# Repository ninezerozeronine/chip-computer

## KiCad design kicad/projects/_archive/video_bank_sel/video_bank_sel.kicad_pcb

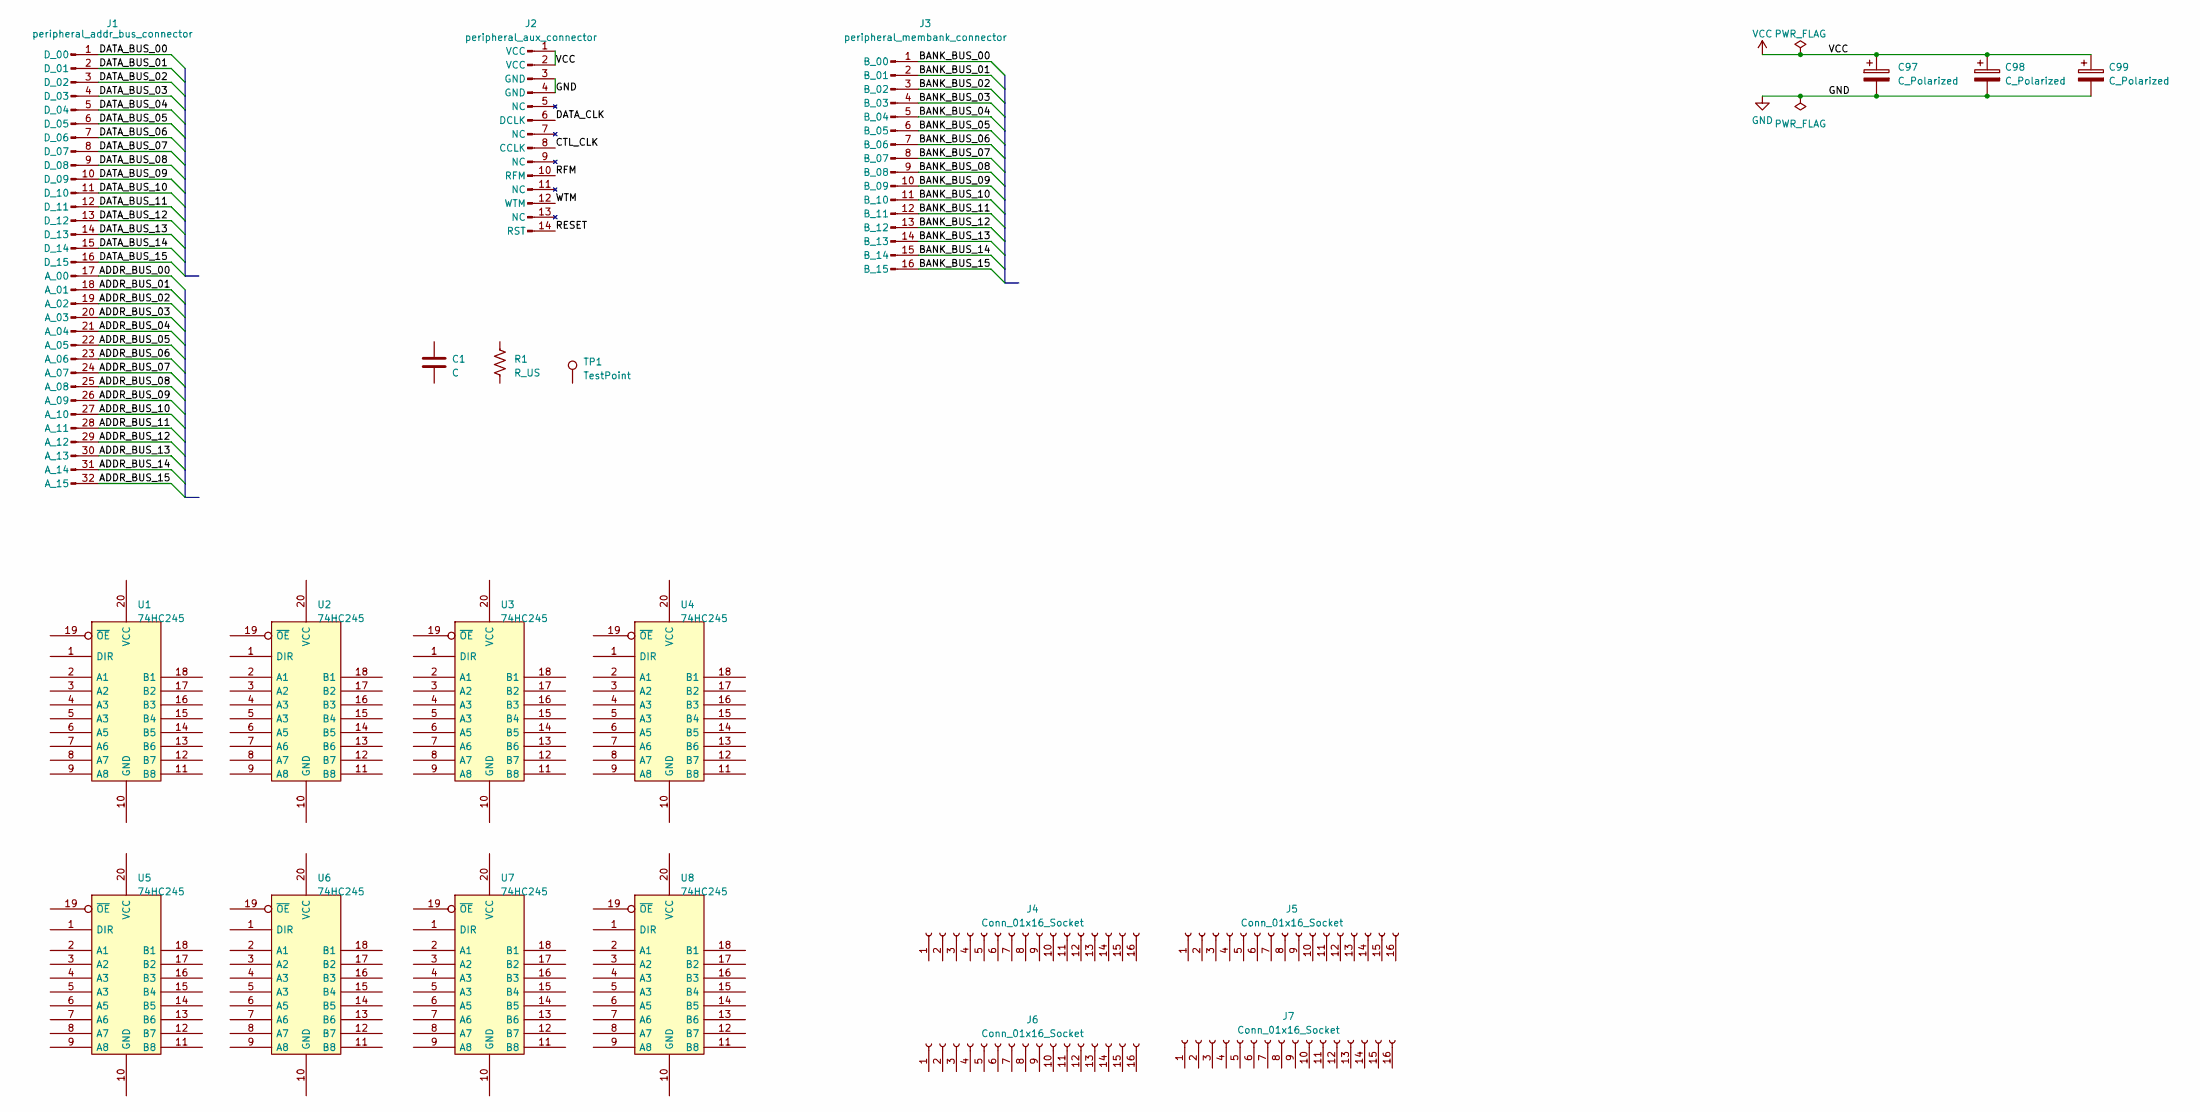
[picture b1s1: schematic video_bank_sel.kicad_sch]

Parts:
C1: C; C_Disc_D5.0mm_W2.5mm_P5.00mm
C97, C98, C99: C_Polarized; CP_Radial_D6.3mm_P2.50mm
J1: peripheral_addr_bus_connector; peripheral-backplane-data-addr-anno
J2: peripheral_aux_connector; peripheral-backplane-aux
J3: peripheral_membank_connector; peripheral-backplane-membank
J4, J5, J6, J7: Conn_01x16_Socket; PinSocket_1x16_P2.54mm_Horizontal
R1: R_US; R_Axial_DIN0207_L6.3mm_D2.5mm_P10.16mm_Horizontal
TP1: TestPoint; Pin_D1.0mm_L10.0mm
U1, U2, U3, U4, U5, U6, U7, U8: 74HC245; DIP-20_W7.62mm_Socket

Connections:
/ADDR_BUS_00: J1.17 (A_00)
/ADDR_BUS_01: J1.18 (A_01)
/ADDR_BUS_02: J1.19 (A_02)
/ADDR_BUS_03: J1.20 (A_03)
/ADDR_BUS_04: J1.21 (A_04)
/ADDR_BUS_05: J1.22 (A_05)
/ADDR_BUS_06: J1.23 (A_06)
/ADDR_BUS_07: J1.24 (A_07)
/ADDR_BUS_08: J1.25 (A_08)
/ADDR_BUS_09: J1.26 (A_09)
/ADDR_BUS_10: J1.27 (A_10)
/ADDR_BUS_11: J1.28 (A_11)
/ADDR_BUS_12: J1.29 (A_12)
/ADDR_BUS_13: J1.30 (A_13)
/ADDR_BUS_14: J1.31 (A_14)
/ADDR_BUS_15: J1.32 (A_15)
/BANK_BUS_00: J3.1 (B_00)
/BANK_BUS_01: J3.2 (B_01)
/BANK_BUS_02: J3.3 (B_02)
/BANK_BUS_03: J3.4 (B_03)
/BANK_BUS_04: J3.5 (B_04)
/BANK_BUS_05: J3.6 (B_05)
/BANK_BUS_06: J3.7 (B_06)
/BANK_BUS_07: J3.8 (B_07)
/BANK_BUS_08: J3.9 (B_08)
/BANK_BUS_09: J3.10 (B_09)
/BANK_BUS_10: J3.11 (B_10)
/BANK_BUS_11: J3.12 (B_11)
/BANK_BUS_12: J3.13 (B_12)
/BANK_BUS_13: J3.14 (B_13)
/BANK_BUS_14: J3.15 (B_14)
/BANK_BUS_15: J3.16 (B_15)
/CTL_CLK: J2.8 (CCLK)
/DATA_BUS_00: J1.1 (D_00)
/DATA_BUS_01: J1.2 (D_01)
/DATA_BUS_02: J1.3 (D_02)
/DATA_BUS_03: J1.4 (D_03)
/DATA_BUS_04: J1.5 (D_04)
/DATA_BUS_05: J1.6 (D_05)
/DATA_BUS_06: J1.7 (D_06)
/DATA_BUS_07: J1.8 (D_07)
/DATA_BUS_08: J1.9 (D_08)
/DATA_BUS_09: J1.10 (D_09)
/DATA_BUS_10: J1.11 (D_10)
/DATA_BUS_11: J1.12 (D_11)
/DATA_BUS_12: J1.13 (D_12)
/DATA_BUS_13: J1.14 (D_13)
/DATA_BUS_14: J1.15 (D_14)
/DATA_BUS_15: J1.16 (D_15)
/DATA_CLK: J2.6 (DCLK)
/RESET: J2.14 (RST)
/RFM: J2.10 (RFM)
/WTM: J2.12 (WTM)
GND: C97.2, C98.2, C99.2, J2.3 (GND), J2.4 (GND)
VCC: C97.1, C98.1, C99.1, J2.1 (VCC), J2.2 (VCC)

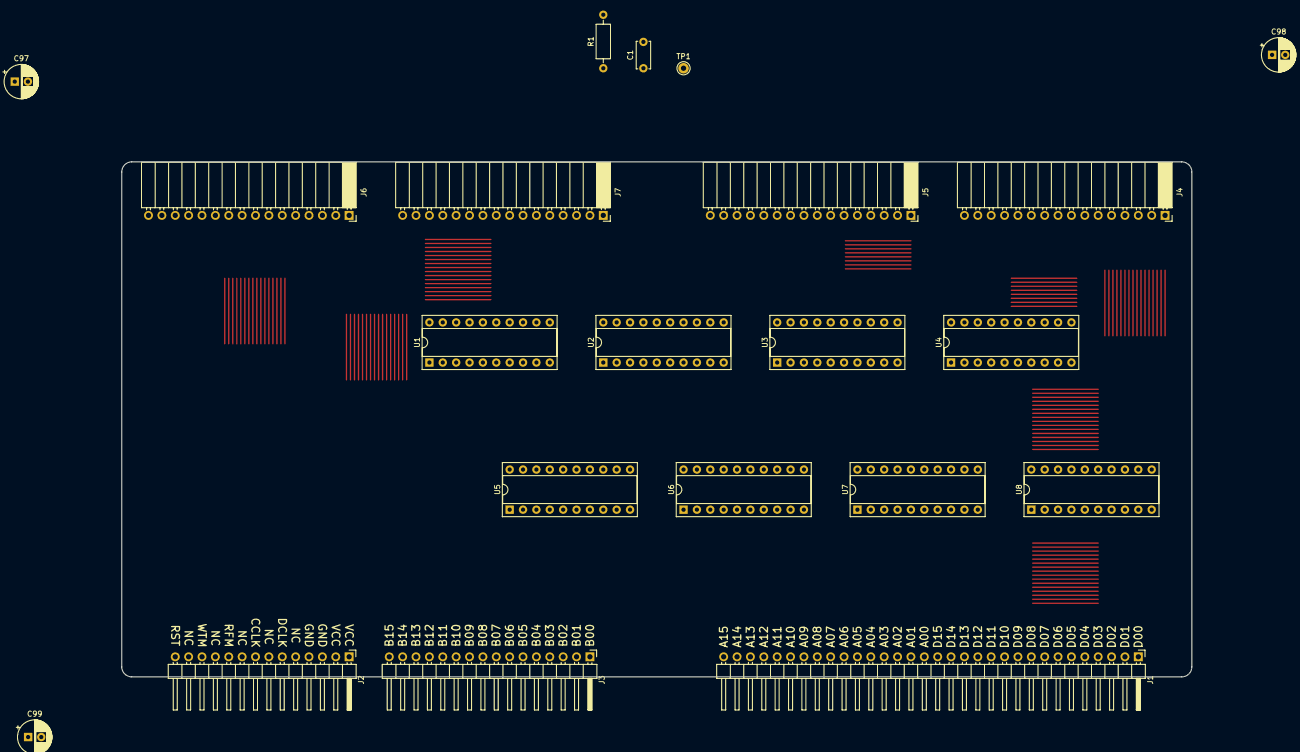
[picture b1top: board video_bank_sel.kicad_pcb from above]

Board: 2 copper layers, 203.2 x 97.8 mm, 21 parts (0 on the bottom side), 2 nets.

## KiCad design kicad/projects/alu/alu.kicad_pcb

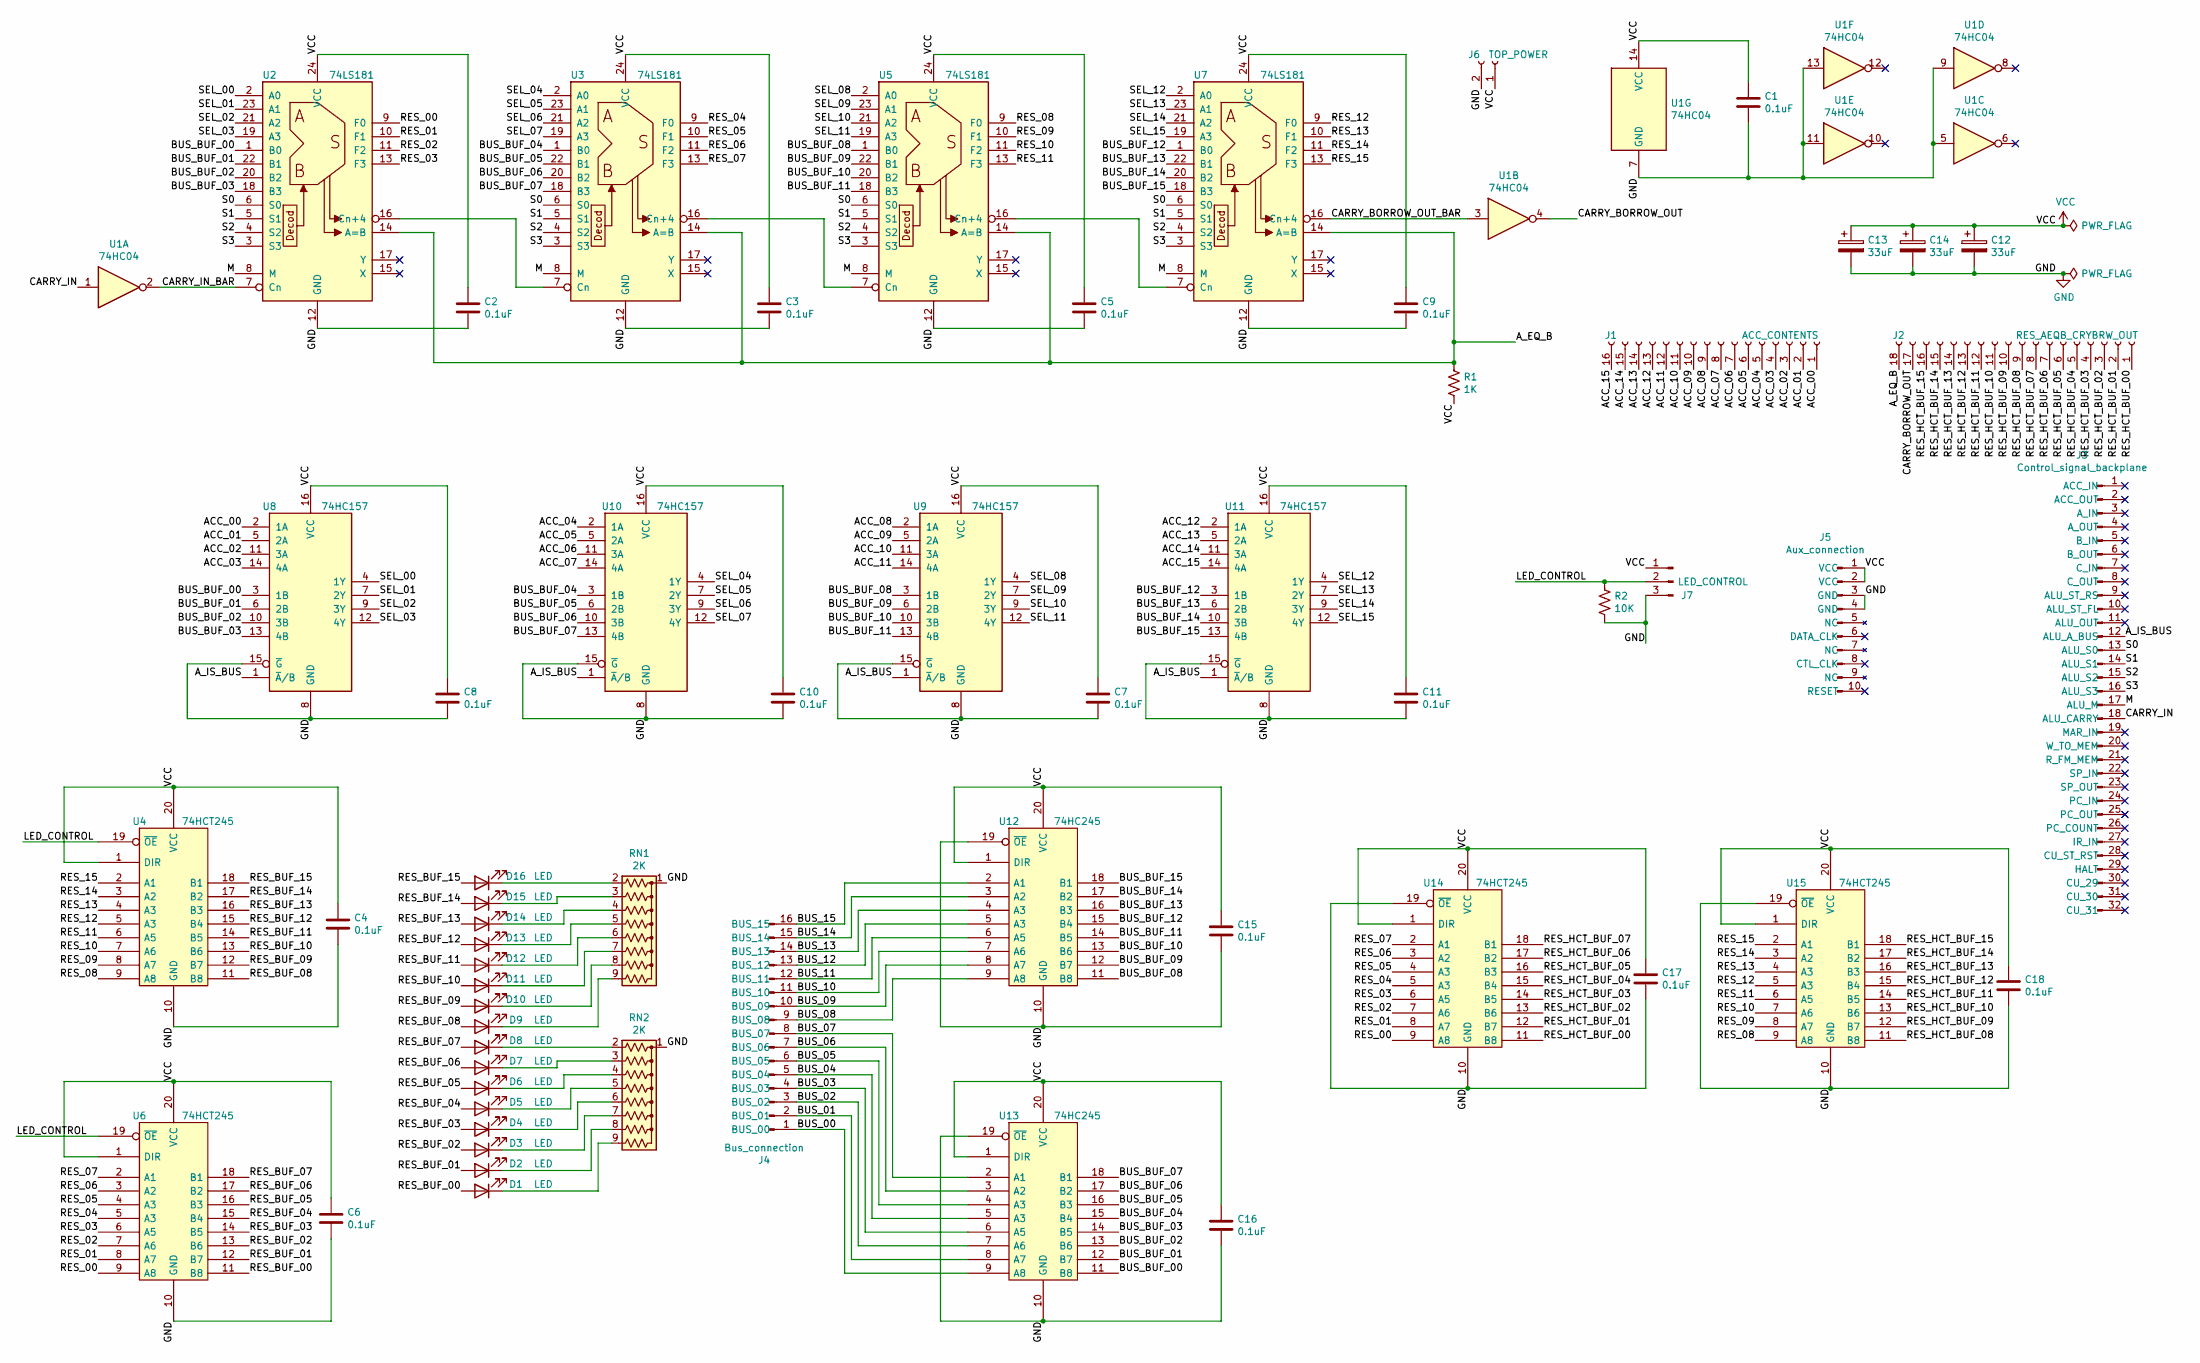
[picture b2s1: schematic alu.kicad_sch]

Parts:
C1, C2, C3, C4, C5, C6, C7, C8, C9, C10, C11, C15, C16, C17, C18: 0.1uF; C_Disc_D4.7mm_W2.5mm_P5.00mm
C12, C13, C14: 33uF; CP_Radial_D6.3mm_P2.50mm
D1, D2, D3, D4, D5, D6, D7, D8, D9, D10, D11, D12, D13, D14, D15, D16: LED; LED_D5.0mm_Horizontal_O3.81mm_Z3.0mm
J1: ACC_CONTENTS; PinSocket_1x16_P2.54mm_Horizontal
J2: RES_AEQB_CRYBRW_OUT; PinSocket_1x18_P2.54mm_Horizontal
J3: Control_signal_backplane; backplane-connector-single-row-annotated
J4: Bus_connection; bus-connection
J5: Aux_connection; aux-connection
J6: TOP_POWER; PinSocket_1x02_P2.54mm_Horizontal
J7: LED_CONTROL; PinHeader_1x03_P2.54mm_Horizontal
R1: 1K; R_Axial_DIN0207_L6.3mm_D2.5mm_P10.16mm_Horizontal
R2: 10K; R_Axial_DIN0207_L6.3mm_D2.5mm_P10.16mm_Horizontal
RN1, RN2: 2K; R_Array_SIP9
U1: 74HC04; DIP-14_W7.62mm_Socket
U2, U3, U5, U7: 74LS181; DIP-24_W15.24mm_Socket
U4, U6, U14, U15: 74HCT245; DIP-20_W7.62mm_Socket
U8, U9, U10, U11: 74HC157; DIP-16_W7.62mm_Socket
U12, U13: 74HC245; DIP-20_W7.62mm_Socket

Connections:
/ACC_00: J1.1, U8.2 (1A)
/ACC_01: J1.2, U8.5 (2A)
/ACC_02: J1.3, U8.11 (3A)
/ACC_03: J1.4, U8.14 (4A)
/ACC_04: J1.5, U10.2 (1A)
/ACC_05: J1.6, U10.5 (2A)
/ACC_06: J1.7, U10.11 (3A)
/ACC_07: J1.8, U10.14 (4A)
/ACC_08: J1.9, U9.2 (1A)
/ACC_09: J1.10, U9.5 (2A)
/ACC_10: J1.11, U9.11 (3A)
/ACC_11: J1.12, U9.14 (4A)
/ACC_12: J1.13, U11.2 (1A)
/ACC_13: J1.14, U11.5 (2A)
/ACC_14: J1.15, U11.11 (3A)
/ACC_15: J1.16, U11.14 (4A)
/A_EQ_B: J2.18, R1.1, U2.14 (A=B), U3.14 (A=B), U5.14 (A=B), U7.14 (A=B)
/A_IS_BUS: J3.12 (ALU_A_BUS), U8.1 (~A/B), U9.1 (~A/B), U10.1 (~A/B), U11.1 (~A/B)
/BUS_00: J4.1 (BUS_00), U13.9 (A8)
/BUS_01: J4.2 (BUS_01), U13.8 (A7)
/BUS_02: J4.3 (BUS_02), U13.7 (A6)
/BUS_03: J4.4 (BUS_03), U13.6 (A5)
/BUS_04: J4.5 (BUS_04), U13.5 (A3)
/BUS_05: J4.6 (BUS_05), U13.4 (A3)
/BUS_06: J4.7 (BUS_06), U13.3 (A2)
/BUS_07: J4.8 (BUS_07), U13.2 (A1)
/BUS_08: J4.9 (BUS_08), U12.9 (A8)
/BUS_09: J4.10 (BUS_09), U12.8 (A7)
/BUS_10: J4.11 (BUS_10), U12.7 (A6)
/BUS_11: J4.12 (BUS_11), U12.6 (A5)
/BUS_12: J4.13 (BUS_12), U12.5 (A3)
/BUS_13: J4.14 (BUS_13), U12.4 (A3)
/BUS_14: J4.15 (BUS_14), U12.3 (A2)
/BUS_15: J4.16 (BUS_15), U12.2 (A1)
/BUS_BUF_00: U2.1 (B0), U8.3 (1B), U13.11 (B8)
/BUS_BUF_01: U2.22 (B1), U8.6 (2B), U13.12 (B7)
/BUS_BUF_02: U2.20 (B2), U8.10 (3B), U13.13 (B6)
/BUS_BUF_03: U2.18 (B3), U8.13 (4B), U13.14 (B5)
/BUS_BUF_04: U3.1 (B0), U10.3 (1B), U13.15 (B4)
/BUS_BUF_05: U3.22 (B1), U10.6 (2B), U13.16 (B3)
/BUS_BUF_06: U3.20 (B2), U10.10 (3B), U13.17 (B2)
/BUS_BUF_07: U3.18 (B3), U10.13 (4B), U13.18 (B1)
/BUS_BUF_08: U5.1 (B0), U9.3 (1B), U12.11 (B8)
/BUS_BUF_09: U5.22 (B1), U9.6 (2B), U12.12 (B7)
/BUS_BUF_10: U5.20 (B2), U9.10 (3B), U12.13 (B6)
/BUS_BUF_11: U5.18 (B3), U9.13 (4B), U12.14 (B5)
/BUS_BUF_12: U7.1 (B0), U11.3 (1B), U12.15 (B4)
/BUS_BUF_13: U7.22 (B1), U11.6 (2B), U12.16 (B3)
/BUS_BUF_14: U7.20 (B2), U11.10 (3B), U12.17 (B2)
/BUS_BUF_15: U7.18 (B3), U11.13 (4B), U12.18 (B1)
/CARRY_BORROW_OUT: J2.17, U1.4
/CARRY_BORROW_OUT_BAR: U1.3, U7.16 (Cn+4)
/CARRY_IN: J3.18 (ALU_CARRY), U1.1
/CARRY_IN_BAR: U1.2, U2.7 (Cn)
/LED_CONTROL: J7.2, R2.1, U4.19 (~OE), U6.19 (~OE)
/M: J3.17 (ALU_M), U2.8 (M), U3.8 (M), U5.8 (M), U7.8 (M)
/RES_00: U2.9 (F0), U6.9 (A8), U14.9 (A8)
/RES_01: U2.10 (F1), U6.8 (A7), U14.8 (A7)
/RES_02: U2.11 (F2), U6.7 (A6), U14.7 (A6)
/RES_03: U2.13 (F3), U6.6 (A5), U14.6 (A5)
/RES_04: U3.9 (F0), U6.5 (A3), U14.5 (A3)
/RES_05: U3.10 (F1), U6.4 (A3), U14.4 (A3)
/RES_06: U3.11 (F2), U6.3 (A2), U14.3 (A2)
/RES_07: U3.13 (F3), U6.2 (A1), U14.2 (A1)
/RES_08: U4.9 (A8), U5.9 (F0), U15.9 (A8)
/RES_09: U4.8 (A7), U5.10 (F1), U15.8 (A7)
/RES_10: U4.7 (A6), U5.11 (F2), U15.7 (A6)
/RES_11: U4.6 (A5), U5.13 (F3), U15.6 (A5)
/RES_12: U4.5 (A3), U7.9 (F0), U15.5 (A3)
/RES_13: U4.4 (A3), U7.10 (F1), U15.4 (A3)
/RES_14: U4.3 (A2), U7.11 (F2), U15.3 (A2)
/RES_15: U4.2 (A1), U7.13 (F3), U15.2 (A1)
/RES_BUF_00: D1.2 (A), U6.11 (B8)
/RES_BUF_01: D2.2 (A), U6.12 (B7)
/RES_BUF_02: D3.2 (A), U6.13 (B6)
/RES_BUF_03: D4.2 (A), U6.14 (B5)
/RES_BUF_04: D5.2 (A), U6.15 (B4)
/RES_BUF_05: D6.2 (A), U6.16 (B3)
/RES_BUF_06: D7.2 (A), U6.17 (B2)
/RES_BUF_07: D8.2 (A), U6.18 (B1)
/RES_BUF_08: D9.2 (A), U4.11 (B8)
/RES_BUF_09: D10.2 (A), U4.12 (B7)
/RES_BUF_10: D11.2 (A), U4.13 (B6)
/RES_BUF_11: D12.2 (A), U4.14 (B5)
/RES_BUF_12: D13.2 (A), U4.15 (B4)
/RES_BUF_13: D14.2 (A), U4.16 (B3)
/RES_BUF_14: D15.2 (A), U4.17 (B2)
/RES_BUF_15: D16.2 (A), U4.18 (B1)
/RES_HCT_BUF_00: J2.1, U14.11 (B8)
/RES_HCT_BUF_01: J2.2, U14.12 (B7)
/RES_HCT_BUF_02: J2.3, U14.13 (B6)
/RES_HCT_BUF_03: J2.4, U14.14 (B5)
/RES_HCT_BUF_04: J2.5, U14.15 (B4)
/RES_HCT_BUF_05: J2.6, U14.16 (B3)
/RES_HCT_BUF_06: J2.7, U14.17 (B2)
/RES_HCT_BUF_07: J2.8, U14.18 (B1)
/RES_HCT_BUF_08: J2.9, U15.11 (B8)
/RES_HCT_BUF_09: J2.10, U15.12 (B7)
/RES_HCT_BUF_10: J2.11, U15.13 (B6)
/RES_HCT_BUF_11: J2.12, U15.14 (B5)
/RES_HCT_BUF_12: J2.13, U15.15 (B4)
/RES_HCT_BUF_13: J2.14, U15.16 (B3)
/RES_HCT_BUF_14: J2.15, U15.17 (B2)
/RES_HCT_BUF_15: J2.16, U15.18 (B1)
/S0: J3.13 (ALU_S0), U2.6 (S0), U3.6 (S0), U5.6 (S0), U7.6 (S0)
/S1: J3.14 (ALU_S1), U2.5 (S1), U3.5 (S1), U5.5 (S1), U7.5 (S1)
/S2: J3.15 (ALU_S2), U2.4 (S2), U3.4 (S2), U5.4 (S2), U7.4 (S2)
/S3: J3.16 (ALU_S3), U2.3 (S3), U3.3 (S3), U5.3 (S3), U7.3 (S3)
/SEL_00: U2.2 (A0), U8.4 (1Y)
/SEL_01: U2.23 (A1), U8.7 (2Y)
/SEL_02: U2.21 (A2), U8.9 (3Y)
/SEL_03: U2.19 (A3), U8.12 (4Y)
/SEL_04: U3.2 (A0), U10.4 (1Y)
/SEL_05: U3.23 (A1), U10.7 (2Y)
/SEL_06: U3.21 (A2), U10.9 (3Y)
/SEL_07: U3.19 (A3), U10.12 (4Y)
/SEL_08: U5.2 (A0), U9.4 (1Y)
/SEL_09: U5.23 (A1), U9.7 (2Y)
/SEL_10: U5.21 (A2), U9.9 (3Y)
/SEL_11: U5.19 (A3), U9.12 (4Y)
/SEL_12: U7.2 (A0), U11.4 (1Y)
/SEL_13: U7.23 (A1), U11.7 (2Y)
/SEL_14: U7.21 (A2), U11.9 (3Y)
/SEL_15: U7.19 (A3), U11.12 (4Y)
GND: C1.2, C2.2, C3.2, C4.2, C5.2, C6.2, C7.2, C8.2, C9.2, C10.2, C11.2, C12.2, C13.2, C14.2, C15.2, C16.2, C17.2, C18.2, J5.3 (GND), J5.4 (GND), J6.2, J7.3, R2.2, RN1.1 (common), RN2.1 (common), U1.5, U1.7 (GND), U1.9, U1.11, U1.13, U2.12 (GND), U3.12 (GND), U4.10 (GND), U5.12 (GND), U6.10 (GND), U7.12 (GND), U8.8 (GND), U8.15 (~G), U9.8 (GND), U9.15 (~G), U10.8 (GND), U10.15 (~G), U11.8 (GND), U11.15 (~G), U12.10 (GND), U12.19 (~OE), U13.10 (GND), U13.19 (~OE), U14.10 (GND), U14.19 (~OE), U15.10 (GND), U15.19 (~OE)
unnamed: D1.1 (K), RN2.9 (R8)
unnamed: D2.1 (K), RN2.8 (R7)
unnamed: D3.1 (K), RN2.7 (R6)
unnamed: D4.1 (K), RN2.6 (R5)
unnamed: D5.1 (K), RN2.5 (R4)
unnamed: D6.1 (K), RN2.4 (R3)
unnamed: D7.1 (K), RN2.3 (R2)
unnamed: D8.1 (K), RN2.2 (R1)
unnamed: D9.1 (K), RN1.9 (R8)
unnamed: D10.1 (K), RN1.8 (R7)
unnamed: D11.1 (K), RN1.7 (R6)
unnamed: D12.1 (K), RN1.6 (R5)
unnamed: D13.1 (K), RN1.5 (R4)
unnamed: D14.1 (K), RN1.4 (R3)
unnamed: D15.1 (K), RN1.3 (R2)
unnamed: D16.1 (K), RN1.2 (R1)
unnamed: U2.16 (Cn+4), U3.7 (Cn)
unnamed: U3.16 (Cn+4), U5.7 (Cn)
unnamed: U5.16 (Cn+4), U7.7 (Cn)
VCC: C1.1, C2.1, C3.1, C4.1, C5.1, C6.1, C7.1, C8.1, C9.1, C10.1, C11.1, C12.1, C13.1, C14.1, C15.1, C16.1, C17.1, C18.1, J5.1 (VCC), J5.2 (VCC), J6.1, J7.1, R1.2, U1.14 (VCC), U2.24 (VCC), U3.24 (VCC), U4.1 (DIR), U4.20 (VCC), U5.24 (VCC), U6.1 (DIR), U6.20 (VCC), U7.24 (VCC), U8.16 (VCC), U9.16 (VCC), U10.16 (VCC), U11.16 (VCC), U12.1 (DIR), U12.20 (VCC), U13.1 (DIR), U13.20 (VCC), U14.1 (DIR), U14.20 (VCC), U15.1 (DIR), U15.20 (VCC)

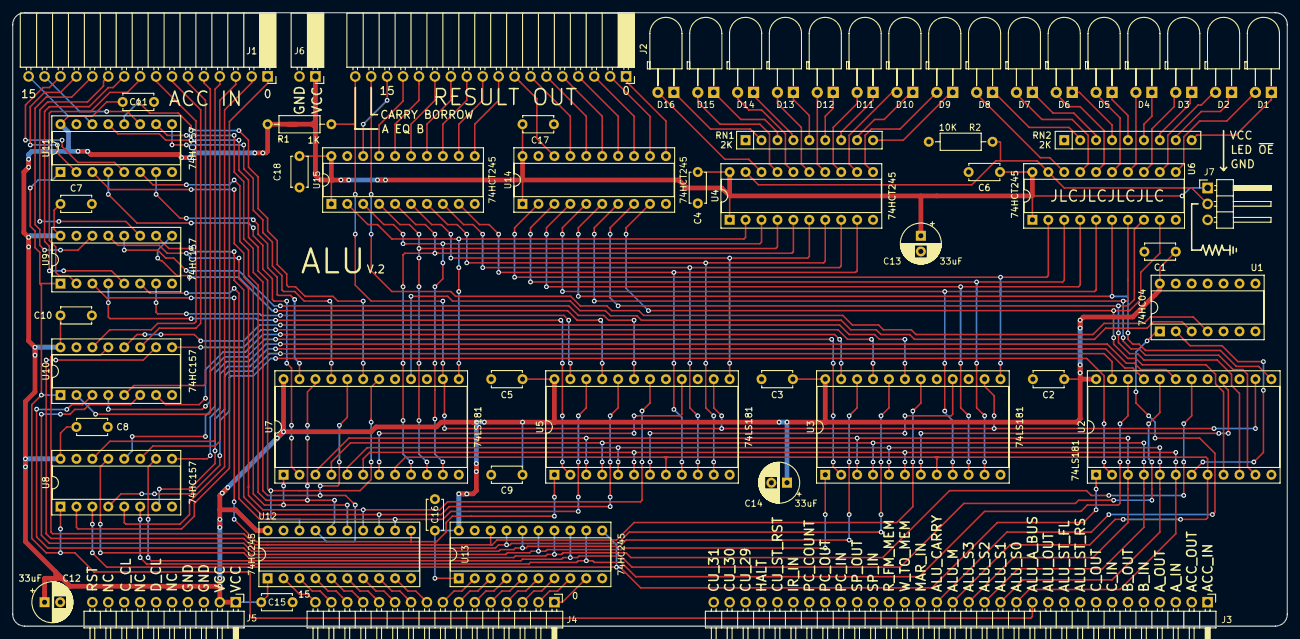
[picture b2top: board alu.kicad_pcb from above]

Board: 2 copper layers, 203.2 x 97.8 mm, 60 parts (0 on the bottom side), 145 nets.

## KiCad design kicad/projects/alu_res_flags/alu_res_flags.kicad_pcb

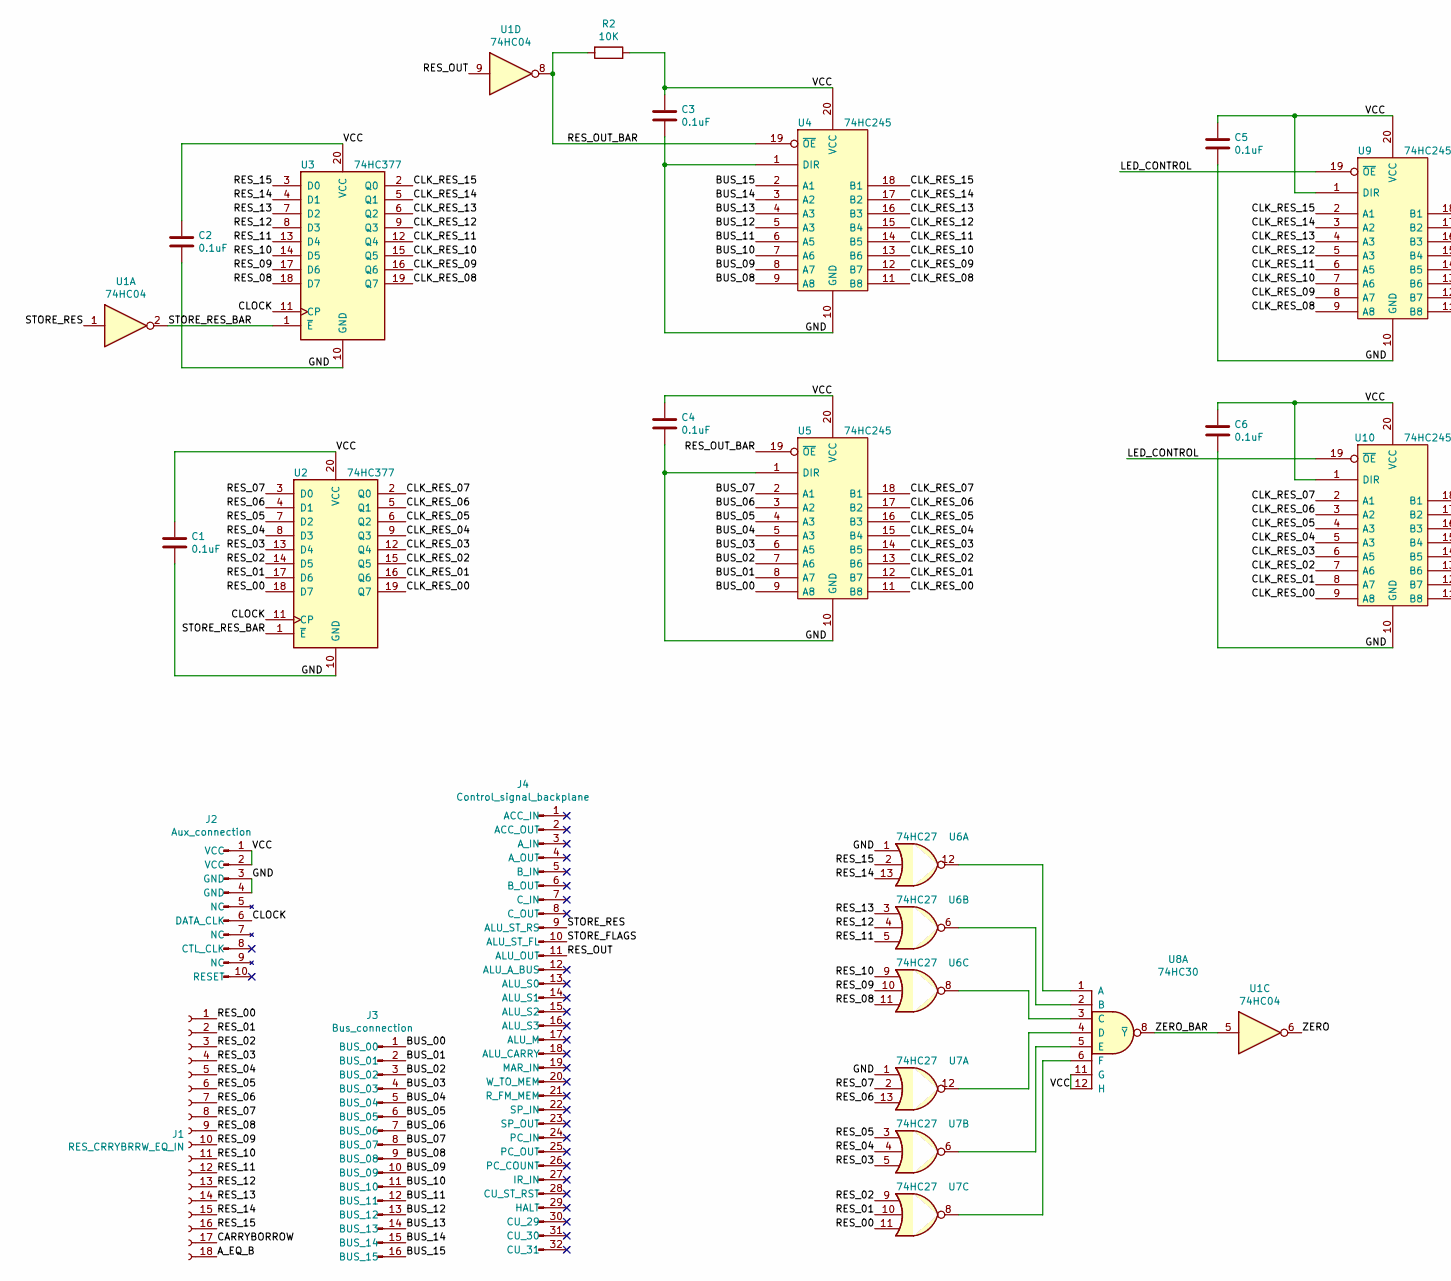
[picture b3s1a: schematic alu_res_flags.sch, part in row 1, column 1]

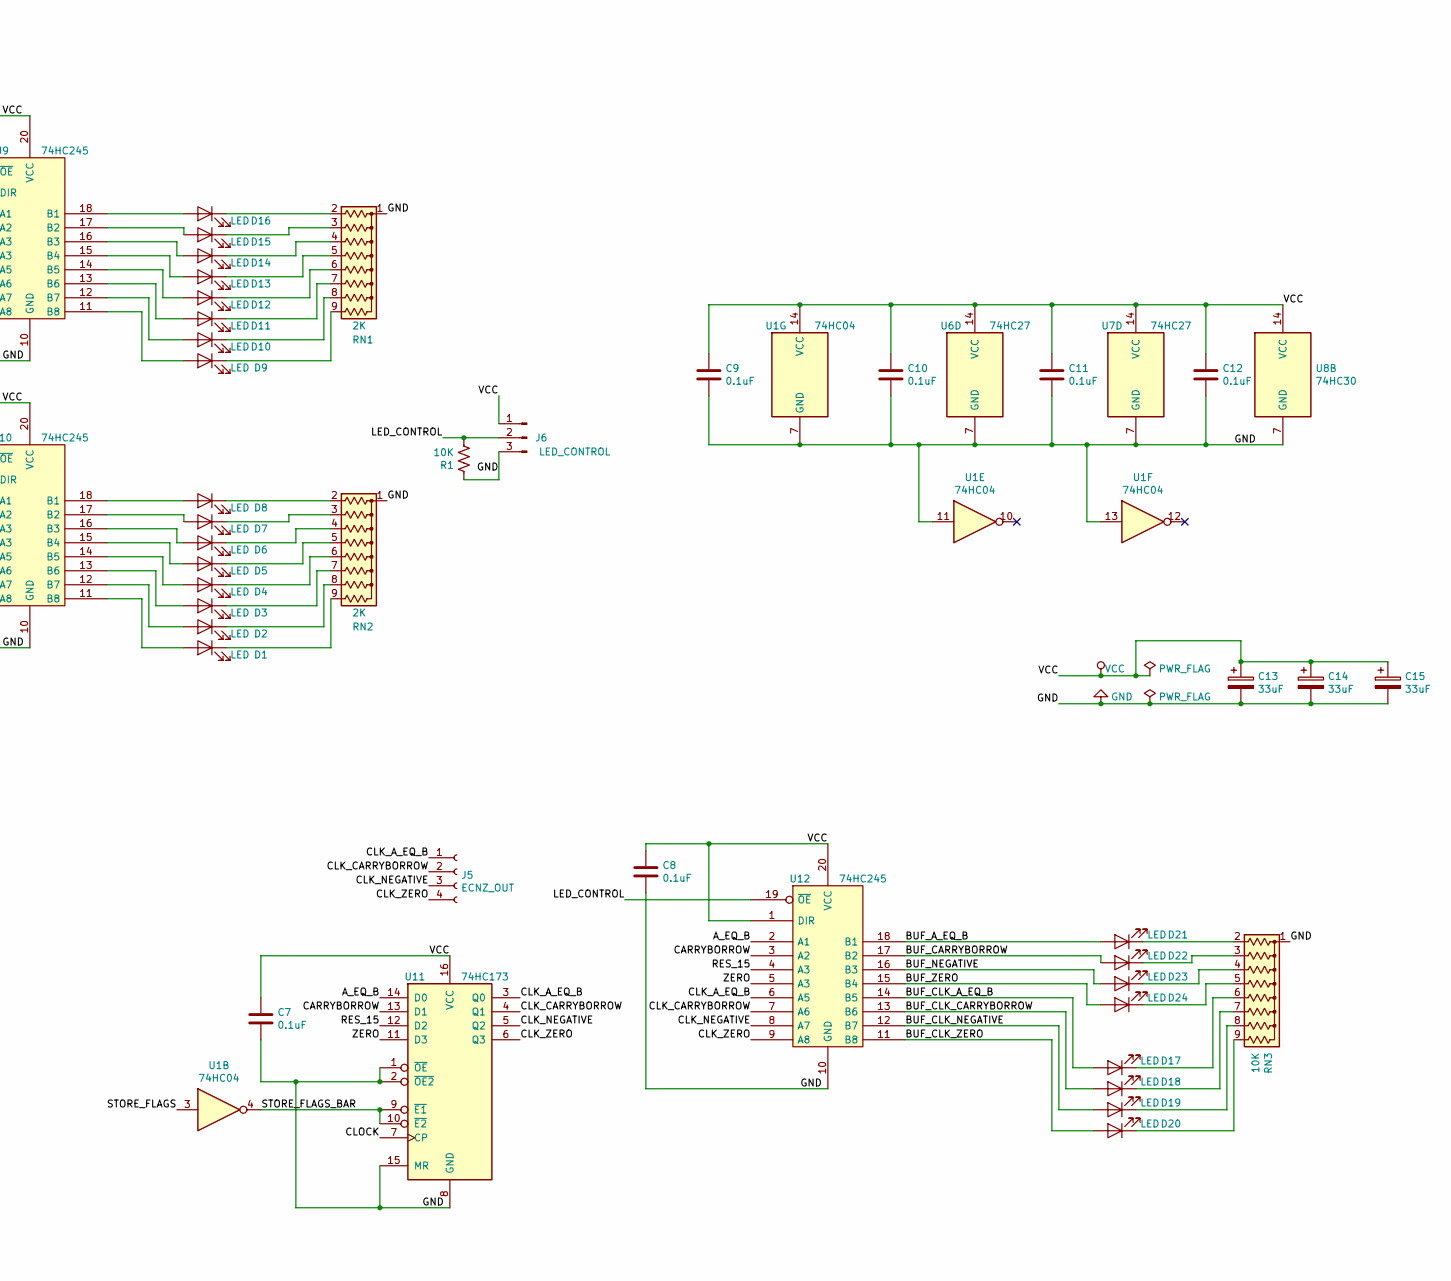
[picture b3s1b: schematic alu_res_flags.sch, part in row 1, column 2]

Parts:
C1, C2, C3, C4, C5, C6, C7, C8, C9, C10, C11, C12: 0.1uF; C_Disc_D4.7mm_W2.5mm_P5.00mm
C13, C14, C15: 33uF; CP_Radial_D6.3mm_P2.50mm
D1, D2, D3, D4, D5, D6, D7, D8, D9, D10, D11, D12, D13, D14, D15, D16, D17, D18, D19, D20, D21, D22, D23, D24: LED; LED_D5.0mm_Horizontal_O3.81mm_Z3.0mm
J1: RES_CRRYBRRW_EQ_IN; PinSocket_1x18_P2.54mm_Horizontal
J2: Aux_connection; aux-connection
J3: Bus_connection; bus-connection
J4: Control_signal_backplane; backplane-connector-single-row-annotated
J5: ECNZ_OUT; PinSocket_1x04_P2.54mm_Horizontal
J6: LED_CONTROL; PinHeader_1x03_P2.54mm_Horizontal
R1, R2: 10K; R_Axial_DIN0207_L6.3mm_D2.5mm_P10.16mm_Horizontal
RN1, RN2: 2K; R_Array_SIP9
RN3: 10K; R_Array_SIP9
U1: 74HC04; DIP-14_W7.62mm_Socket
U2, U3: 74HC377; DIP-20_W7.62mm_Socket
U4, U5, U9, U10, U12: 74HC245; DIP-20_W7.62mm_Socket
U6, U7: 74HC27; DIP-14_W7.62mm_Socket
U8: 74HC30; DIP-14_W7.62mm_Socket
U11: 74HC173; DIP-16_W7.62mm_Socket

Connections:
/A_EQ_B: J1.18, U11.14 (D0), U12.2 (A1)
/BUF_A_EQ_B: D21.2 (A), U12.18 (B1)
/BUF_CARRYBORROW: D22.2 (A), U12.17 (B2)
/BUF_CLK_A_EQ_B: D17.2 (A), U12.14 (B5)
/BUF_CLK_CARRYBORROW: D18.2 (A), U12.13 (B6)
/BUF_CLK_NEGATIVE: D19.2 (A), U12.12 (B7)
/BUF_CLK_ZERO: D20.2 (A), U12.11 (B8)
/BUF_NEGATIVE: D23.2 (A), U12.16 (B3)
/BUF_ZERO: D24.2 (A), U12.15 (B4)
/BUS_00: J3.1 (BUS_00), U5.9 (A8)
/BUS_01: J3.2 (BUS_01), U5.8 (A7)
/BUS_02: J3.3 (BUS_02), U5.7 (A6)
/BUS_03: J3.4 (BUS_03), U5.6 (A5)
/BUS_04: J3.5 (BUS_04), U5.5 (A3)
/BUS_05: J3.6 (BUS_05), U5.4 (A3)
/BUS_06: J3.7 (BUS_06), U5.3 (A2)
/BUS_07: J3.8 (BUS_07), U5.2 (A1)
/BUS_08: J3.9 (BUS_08), U4.9 (A8)
/BUS_09: J3.10 (BUS_09), U4.8 (A7)
/BUS_10: J3.11 (BUS_10), U4.7 (A6)
/BUS_11: J3.12 (BUS_11), U4.6 (A5)
/BUS_12: J3.13 (BUS_12), U4.5 (A3)
/BUS_13: J3.14 (BUS_13), U4.4 (A3)
/BUS_14: J3.15 (BUS_14), U4.3 (A2)
/BUS_15: J3.16 (BUS_15), U4.2 (A1)
/CARRYBORROW: J1.17, U11.13 (D1), U12.3 (A2)
/CLK_A_EQ_B: J5.1, U11.3 (Q0), U12.6 (A5)
/CLK_CARRYBORROW: J5.2, U11.4 (Q1), U12.7 (A6)
/CLK_NEGATIVE: J5.3, U11.5 (Q2), U12.8 (A7)
/CLK_RES_00: U2.19 (Q7), U5.11 (B8), U10.9 (A8)
/CLK_RES_01: U2.16 (Q6), U5.12 (B7), U10.8 (A7)
/CLK_RES_02: U2.15 (Q5), U5.13 (B6), U10.7 (A6)
/CLK_RES_03: U2.12 (Q4), U5.14 (B5), U10.6 (A5)
/CLK_RES_04: U2.9 (Q3), U5.15 (B4), U10.5 (A3)
/CLK_RES_05: U2.6 (Q2), U5.16 (B3), U10.4 (A3)
/CLK_RES_06: U2.5 (Q1), U5.17 (B2), U10.3 (A2)
/CLK_RES_07: U2.2 (Q0), U5.18 (B1), U10.2 (A1)
/CLK_RES_08: U3.19 (Q7), U4.11 (B8), U9.9 (A8)
/CLK_RES_09: U3.16 (Q6), U4.12 (B7), U9.8 (A7)
/CLK_RES_10: U3.15 (Q5), U4.13 (B6), U9.7 (A6)
/CLK_RES_11: U3.12 (Q4), U4.14 (B5), U9.6 (A5)
/CLK_RES_12: U3.9 (Q3), U4.15 (B4), U9.5 (A3)
/CLK_RES_13: U3.6 (Q2), U4.16 (B3), U9.4 (A3)
/CLK_RES_14: U3.5 (Q1), U4.17 (B2), U9.3 (A2)
/CLK_RES_15: U3.2 (Q0), U4.18 (B1), U9.2 (A1)
/CLK_ZERO: J5.4, U11.6 (Q3), U12.9 (A8)
/CLOCK: J2.6 (DATA_CLK), U2.11 (CP), U3.11 (CP), U11.7 (CP)
/LED_CONTROL: J6.2, R1.2, U9.19 (~OE), U10.19 (~OE), U12.19 (~OE)
/RES_00: J1.1, U2.18 (D7), U7.11
/RES_01: J1.2, U2.17 (D6), U7.10
/RES_02: J1.3, U2.14 (D5), U7.9
/RES_03: J1.4, U2.13 (D4), U7.5
/RES_04: J1.5, U2.8 (D3), U7.4
/RES_05: J1.6, U2.7 (D2), U7.3
/RES_06: J1.7, U2.4 (D1), U7.13
/RES_07: J1.8, U2.3 (D0), U7.2
/RES_08: J1.9, U3.18 (D7), U6.11
/RES_09: J1.10, U3.17 (D6), U6.10
/RES_10: J1.11, U3.14 (D5), U6.9
/RES_11: J1.12, U3.13 (D4), U6.5
/RES_12: J1.13, U3.8 (D3), U6.4
/RES_13: J1.14, U3.7 (D2), U6.3
/RES_14: J1.15, U3.4 (D1), U6.13
/RES_15: J1.16, U3.3 (D0), U6.2, U11.12 (D2), U12.4 (A3)
/RES_OUT: J4.11 (ALU_OUT), U1.9
/RES_OUT_BAR: R2.2, U1.8, U4.19 (~OE), U5.19 (~OE)
/STORE_FLAGS: J4.10 (ALU_ST_FL), U1.3
/STORE_FLAGS_BAR: U1.4, U11.9 (~E1), U11.10 (~E2)
/STORE_RES: J4.9 (ALU_ST_RS), U1.1
/STORE_RES_BAR: U1.2, U2.1 (~E), U3.1 (~E)
/ZERO: U1.6, U11.11 (D3), U12.5 (A3)
/ZERO_BAR: U1.5, U8.8 (~Y)
GND: C1.2, C2.2, C3.2, C4.2, C5.2, C6.2, C7.2, C8.2, C9.2, C10.2, C11.2, C12.2, C13.2, C14.2, C15.2, J2.3 (GND), J2.4 (GND), J6.3, R1.1, RN1.1 (common), RN2.1 (common), RN3.1 (common), U1.7 (GND), U1.11, U1.13, U2.10 (GND), U3.10 (GND), U4.1 (DIR), U4.10 (GND), U5.1 (DIR), U5.10 (GND), U6.1, U6.7 (GND), U7.1, U7.7 (GND), U8.7 (GND), U9.10 (GND), U10.10 (GND), U11.1 (~OE), U11.2 (~OE2), U11.8 (GND), U11.15 (MR), U12.10 (GND)
unnamed: D1.1 (K), RN2.9 (R8)
unnamed: D1.2 (A), U10.11 (B8)
unnamed: D2.1 (K), RN2.8 (R7)
unnamed: D2.2 (A), U10.12 (B7)
unnamed: D3.1 (K), RN2.7 (R6)
unnamed: D3.2 (A), U10.13 (B6)
unnamed: D4.1 (K), RN2.6 (R5)
unnamed: D4.2 (A), U10.14 (B5)
unnamed: D5.1 (K), RN2.5 (R4)
unnamed: D5.2 (A), U10.15 (B4)
unnamed: D6.1 (K), RN2.4 (R3)
unnamed: D6.2 (A), U10.16 (B3)
unnamed: D7.1 (K), RN2.3 (R2)
unnamed: D7.2 (A), U10.17 (B2)
unnamed: D8.1 (K), RN2.2 (R1)
unnamed: D8.2 (A), U10.18 (B1)
unnamed: D9.1 (K), RN1.9 (R8)
unnamed: D9.2 (A), U9.11 (B8)
unnamed: D10.1 (K), RN1.8 (R7)
unnamed: D10.2 (A), U9.12 (B7)
unnamed: D11.1 (K), RN1.7 (R6)
unnamed: D11.2 (A), U9.13 (B6)
unnamed: D12.1 (K), RN1.6 (R5)
unnamed: D12.2 (A), U9.14 (B5)
unnamed: D13.1 (K), RN1.5 (R4)
unnamed: D13.2 (A), U9.15 (B4)
unnamed: D14.1 (K), RN1.4 (R3)
unnamed: D14.2 (A), U9.16 (B3)
unnamed: D15.1 (K), RN1.3 (R2)
unnamed: D15.2 (A), U9.17 (B2)
unnamed: D16.1 (K), RN1.2 (R1)
unnamed: D16.2 (A), U9.18 (B1)
unnamed: D17.1 (K), RN3.6 (R5)
unnamed: D18.1 (K), RN3.7 (R6)
unnamed: D19.1 (K), RN3.8 (R7)
unnamed: D20.1 (K), RN3.9 (R8)
unnamed: D21.1 (K), RN3.2 (R1)
unnamed: D22.1 (K), RN3.3 (R2)
unnamed: D23.1 (K), RN3.4 (R3)
unnamed: D24.1 (K), RN3.5 (R4)
unnamed: U6.6, U8.2 (B)
unnamed: U6.8, U8.3 (C)
unnamed: U6.12, U8.1 (A)
unnamed: U7.6, U8.5 (E)
unnamed: U7.8, U8.6 (F)
unnamed: U7.12, U8.4 (D)
VCC: C1.1, C2.1, C3.1, C4.1, C5.1, C6.1, C7.1, C8.1, C9.1, C10.1, C11.1, C12.1, C13.1, C14.1, C15.1, J2.1 (VCC), J2.2 (VCC), J6.1, R2.1, U1.14 (VCC), U2.20 (VCC), U3.20 (VCC), U4.20 (VCC), U5.20 (VCC), U6.14 (VCC), U7.14 (VCC), U8.11 (G), U8.12 (H), U8.14 (VCC), U9.1 (DIR), U9.20 (VCC), U10.1 (DIR), U10.20 (VCC), U11.16 (VCC), U12.1 (DIR), U12.20 (VCC)

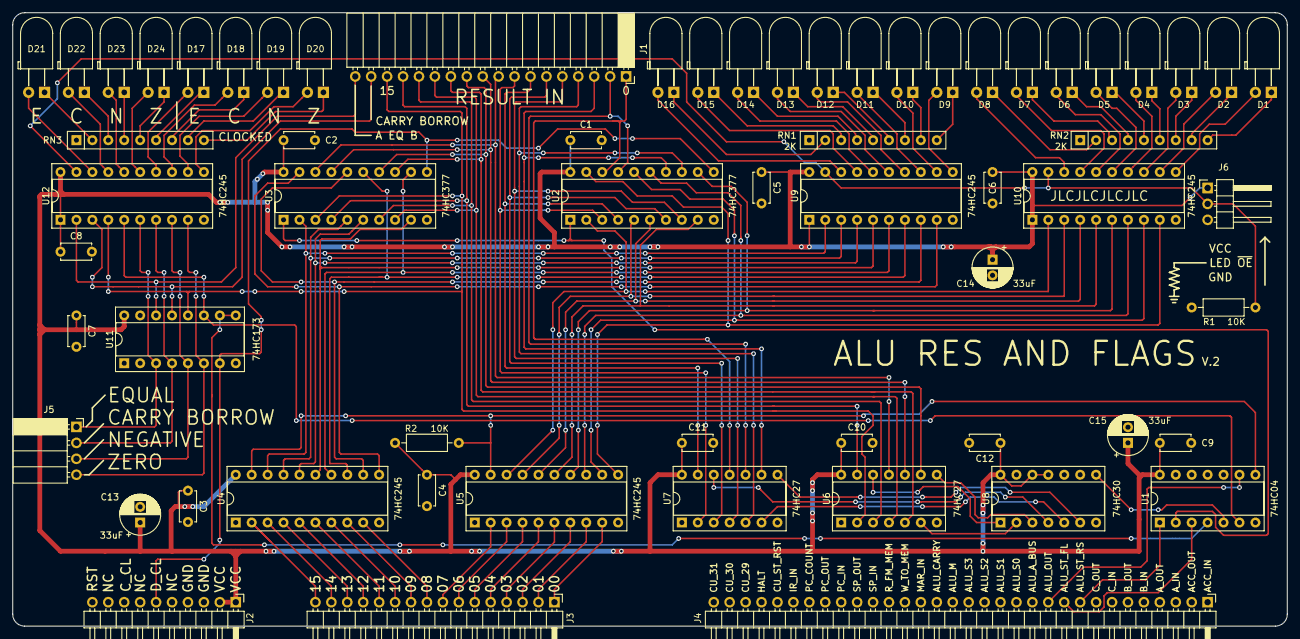
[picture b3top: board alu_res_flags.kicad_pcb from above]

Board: 2 copper layers, 203.2 x 97.8 mm, 62 parts (0 on the bottom side), 120 nets.
